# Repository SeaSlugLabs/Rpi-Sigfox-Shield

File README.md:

# Rpi-Sigfox-Shield
Documentation for Raspberry Pi Sigfox Board

The Wisol WSSFM10R2 is a Sigfox Module based on [Onsemi AX-SFUS](http://www.onsemi.com/pub/Collateral/AX-SFUS-D.PDF)

The WSSFM10R2 uses a UART interface. Simple commands are used to operate the module(see DataSheet).

This Board fits on Raspberry Pi 3, 2, B+, A+, Zero and Zero W.

Find on this repository the information about board. And some python examples to send information via Sigfox Network.

Dont forget to buy our products at [Sea Slug Labs IoT Maker Store](http://www.seasluglabs.io)

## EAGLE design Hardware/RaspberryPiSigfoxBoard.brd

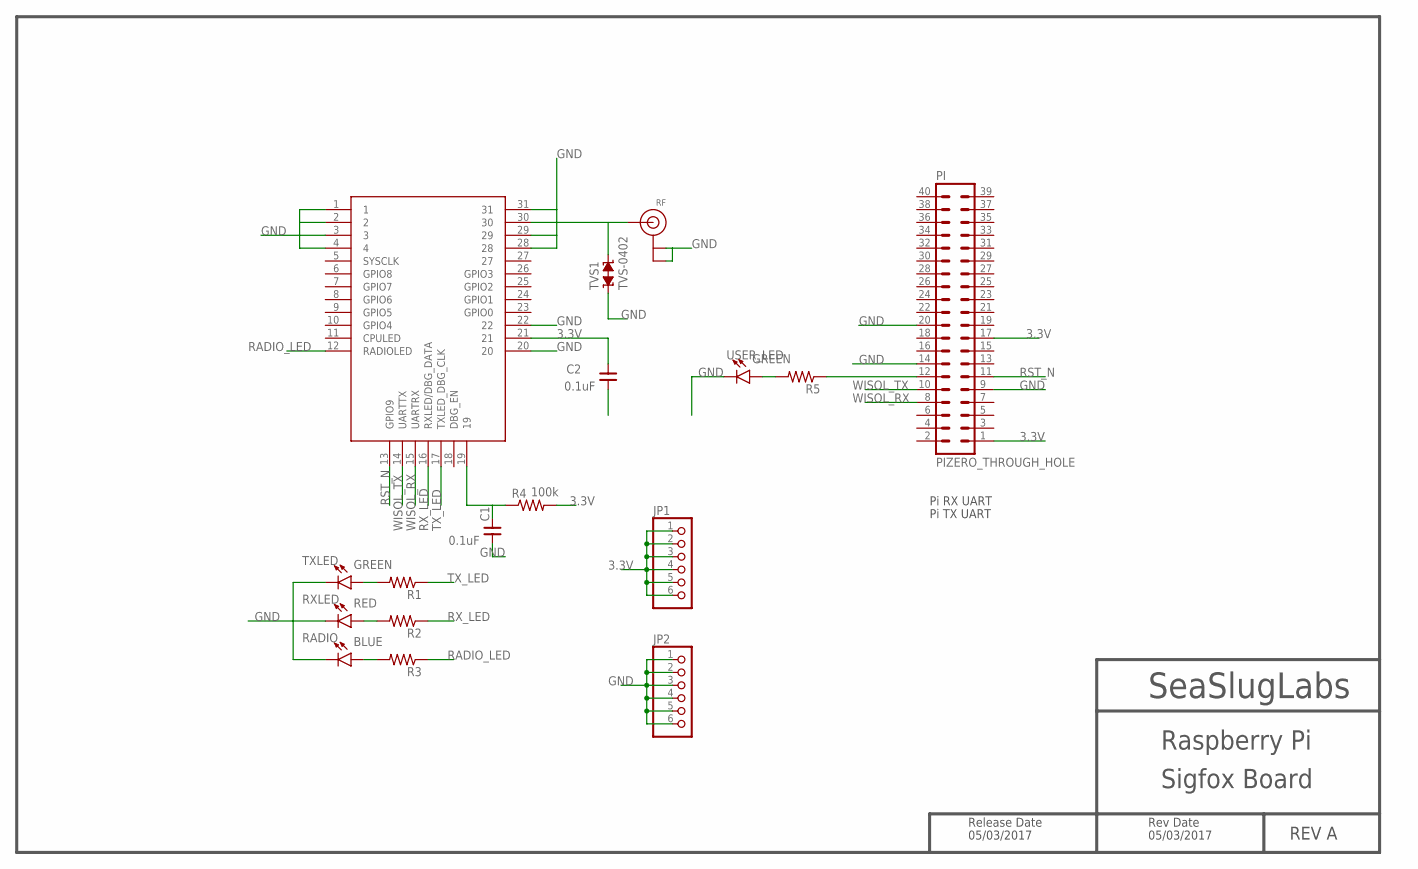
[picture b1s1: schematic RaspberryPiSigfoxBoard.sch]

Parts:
C1, C2: 0.1uF; 0402
JP1, JP2: PINHD-1X6B; 1X06-BIG
PI: PIZERO_THROUGH_HOLE; PIZERO_THOUGH_HOLE
R1, R2, R3, R5: R-US_R0402; R0402
R4: 100k; R0402
RADIO: BLUE; LED-0603
RF: ANTENNA_U.FL; U.FL
RXLED: RED; LED-0603
TVS1: TVS-0402; TVS0402
TXLED: GREEN; LED-0603
USER_LED: GREEN; LED-0603
WSSFM10R2: WSSFM10R2/R4WSSFM10R2R4; WISOL

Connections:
3.3V: C2.2, JP1.1, JP1.2, JP1.3, JP1.4, JP1.5, JP1.6, PI.1, PI.17, R4.2, WSSFM10R2.21
GND: C1.1, C2.1, JP2.1, JP2.2, JP2.3, JP2.4, JP2.5, JP2.6, PI.9, PI.14, PI.20, RADIO.C, RF.1 (GND), RF.2 (GND), RXLED.C, TVS1.1, TXLED.C, USER_LED.C, WSSFM10R2.1, WSSFM10R2.2, WSSFM10R2.3, WSSFM10R2.4, WSSFM10R2.20, WSSFM10R2.22, WSSFM10R2.28, WSSFM10R2.29, WSSFM10R2.31
unnamed: C1.2, R4.1, WSSFM10R2.19
unnamed: R1.2, TXLED.A
unnamed: R2.2, RXLED.A
unnamed: R3.2, RADIO.A
unnamed: RF.3 (SIGNAL), TVS1.2, WSSFM10R2.30
unnamed: PI.12, R5.1
unnamed: R5.2, USER_LED.A
RADIO_LED: R3.1, WSSFM10R2.12 (RADIOLED)
RST_N: PI.11, WSSFM10R2.13 (GPIO9)
RX_LED: R2.1, WSSFM10R2.16 (RXLED/DBG_DATA)
TX_LED: R1.1, WSSFM10R2.17 (TXLED_DBG_CLK)
WISOL_RX: PI.8, WSSFM10R2.15 (UARTRX)
WISOL_TX: PI.10, WSSFM10R2.14 (UARTTX)

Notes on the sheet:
Pi TX UART
Pi RX UART
SeaSlugLabs
Raspberry Pi
REV A
Sigfox Board
Release Date
05/03/2017
Rev Date

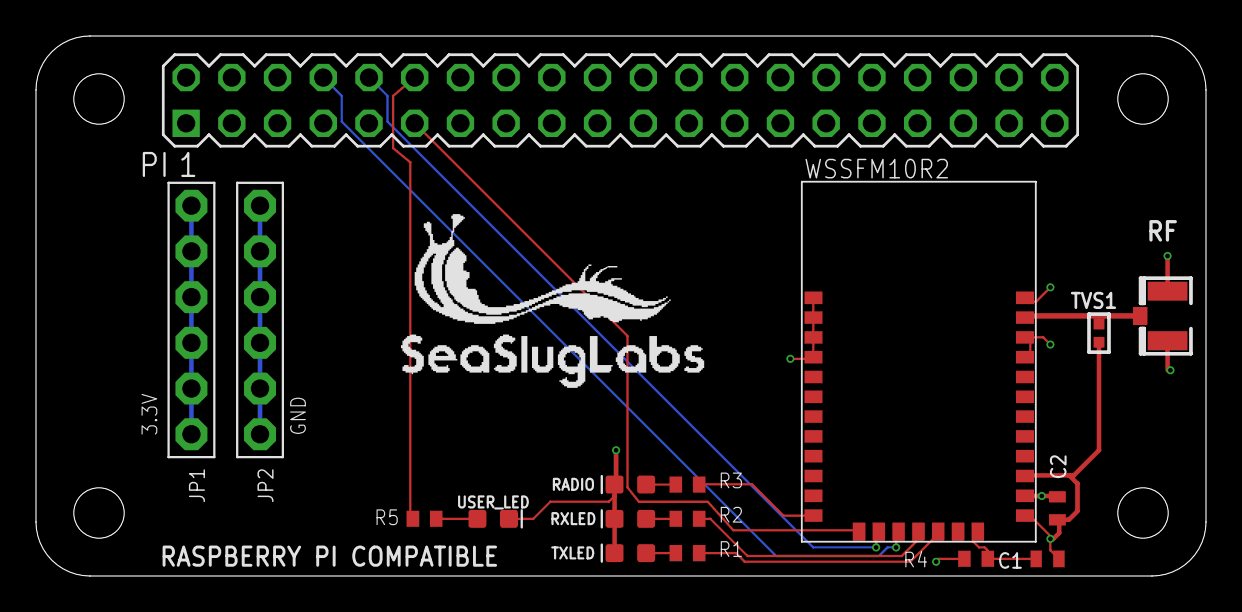
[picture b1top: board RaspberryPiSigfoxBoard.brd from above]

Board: 4 copper layers, 65.0 x 30.0 mm, 17 parts (0 on the bottom side), 15 nets.

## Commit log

2017-05-04 Add Design Files
2017-05-04 Raspberry Pi python Example
2017-05-04 Example screenshot from the python script
2017-08-15 Added AT$RC command before sending AT$SF

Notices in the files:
parts and their libraries:
supressor: Copyright (C) 2009, Bob Starr
